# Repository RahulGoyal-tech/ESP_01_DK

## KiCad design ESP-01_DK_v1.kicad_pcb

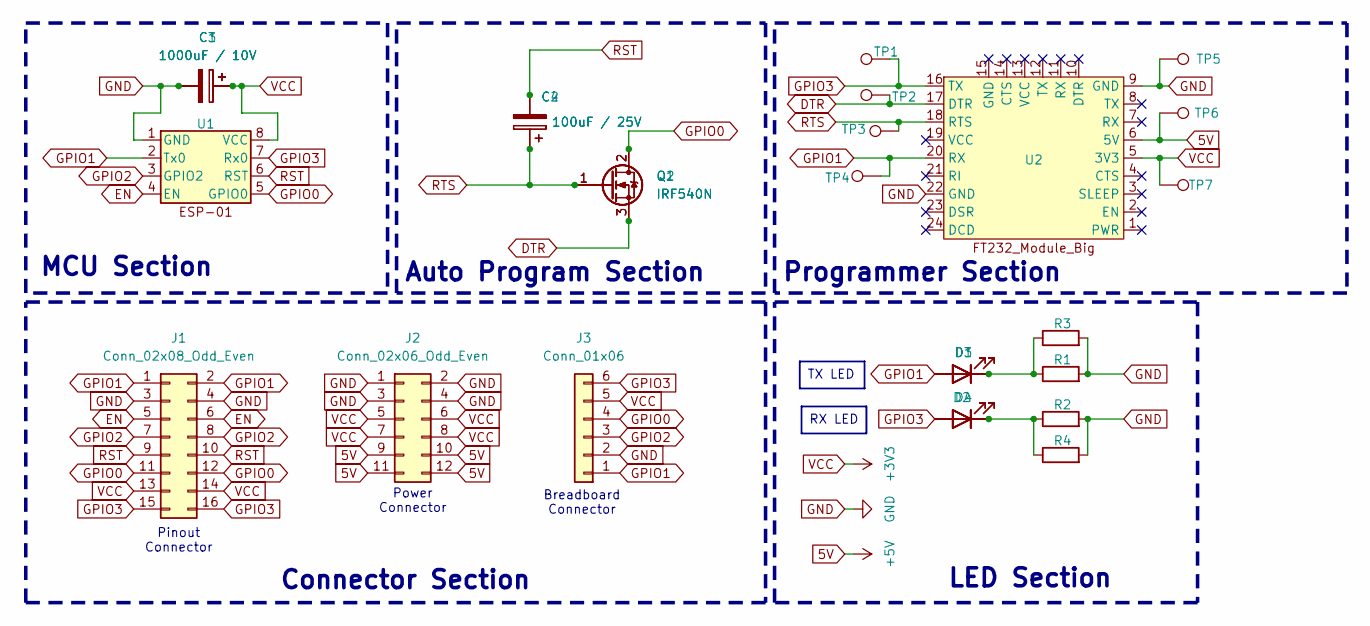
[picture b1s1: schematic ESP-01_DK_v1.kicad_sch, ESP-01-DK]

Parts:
C1: 1000uF / 10V; C_Radial_D10.0mm_H16.0mm_P5.00mm
C2: 100uF / 25V; C_Radial_D6.3mm_H11.0mm_P2.50mm
C3: 1000uF / 10V; C_Radial_D8.0mm_H11.5mm_P3.50mm
C4: 100uF / 25V; C_Radial_D4.0mm_H7.0mm_P1.50mm
D1, D2: LED; LED_D5.0mm
D3, D4: LED; LED_0805_2012Metric
J1: Conn_02x08_Odd_Even; PinHeader_2x08_P2.54mm_Vertical
J2: Conn_02x06_Odd_Even; PinHeader_2x06_P2.54mm_Vertical
J3: Conn_01x06; PinHeader_1x06_P2.54mm_Vertical
Q1: IRF540N; TO-220-3_Vertical
Q2: IRF540N; TO-252-2
R1, R2: 330; R_Axial_DIN0207_L6.3mm_D2.5mm_P10.16mm_Horizontal
R3, R4: 330; R_0805_2012Metric_Pad1.20x1.40mm_HandSolder
TP1, TP2: TestPoint_Bridge_Pitch2.54mm_Drill0.7mm
TP3, TP4, TP5, TP6, TP7: TestPoint; TestPoint_Bridge_Pitch2.54mm_Drill0.7mm
U1: PinHeader_2x04_P2.54mm_Vertical
U2: FT232_Module_Big

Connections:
5V: J2.9, J2.10, J2.11, J2.12, TP6.1, U2.6 (5V)
DTR: Q1.3 (S), Q2.3 (S), TP2.1, U2.17 (DTR)
EN: J1.5, J1.6, U1.4 (EN)
GND: C1.2, C3.2, J1.3, J1.4, J2.1, J2.2, J2.3, J2.4, J3.2, R1.2, R2.2, R3.2, R4.2, TP5.1, U1.1 (GND), U2.9 (GND), U2.22 (GND)
GPIO0: J1.11, J1.12, J3.4, Q1.2 (D), Q2.2 (D), U1.5 (GPIO0)
GPIO1: D1.2 (A), D3.2 (A), J1.1, J1.2, J3.1, TP4.1, U1.2 (Tx0), U2.20 (RX)
GPIO2: J1.7, J1.8, J3.3, U1.3 (GPIO2)
GPIO3: D2.2 (A), D4.2 (A), J1.15, J1.16, J3.6, TP1.1, U1.7 (Rx0), U2.16 (TX)
unnamed: D1.1 (K), D3.1 (K), R1.1, R3.1
unnamed: D2.1 (K), D4.1 (K), R2.1, R4.1
RST: C2.2, C4.2, J1.9, J1.10, U1.6 (RST)
RTS: C2.1, C4.1, Q1.1 (G), Q2.1 (G), TP3.1, U2.18 (RTS)
VCC: C1.1, C3.1, J1.13, J1.14, J2.5, J2.6, J2.7, J2.8, J3.5, TP7.1, U1.8 (VCC), U2.5 (3V3)

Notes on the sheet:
RX LED
TX LED
Auto Program Section
Programmer Section
Breadboard Connector
Connector Section
Power Connector
MCU Section
LED Section
Pinout Connector

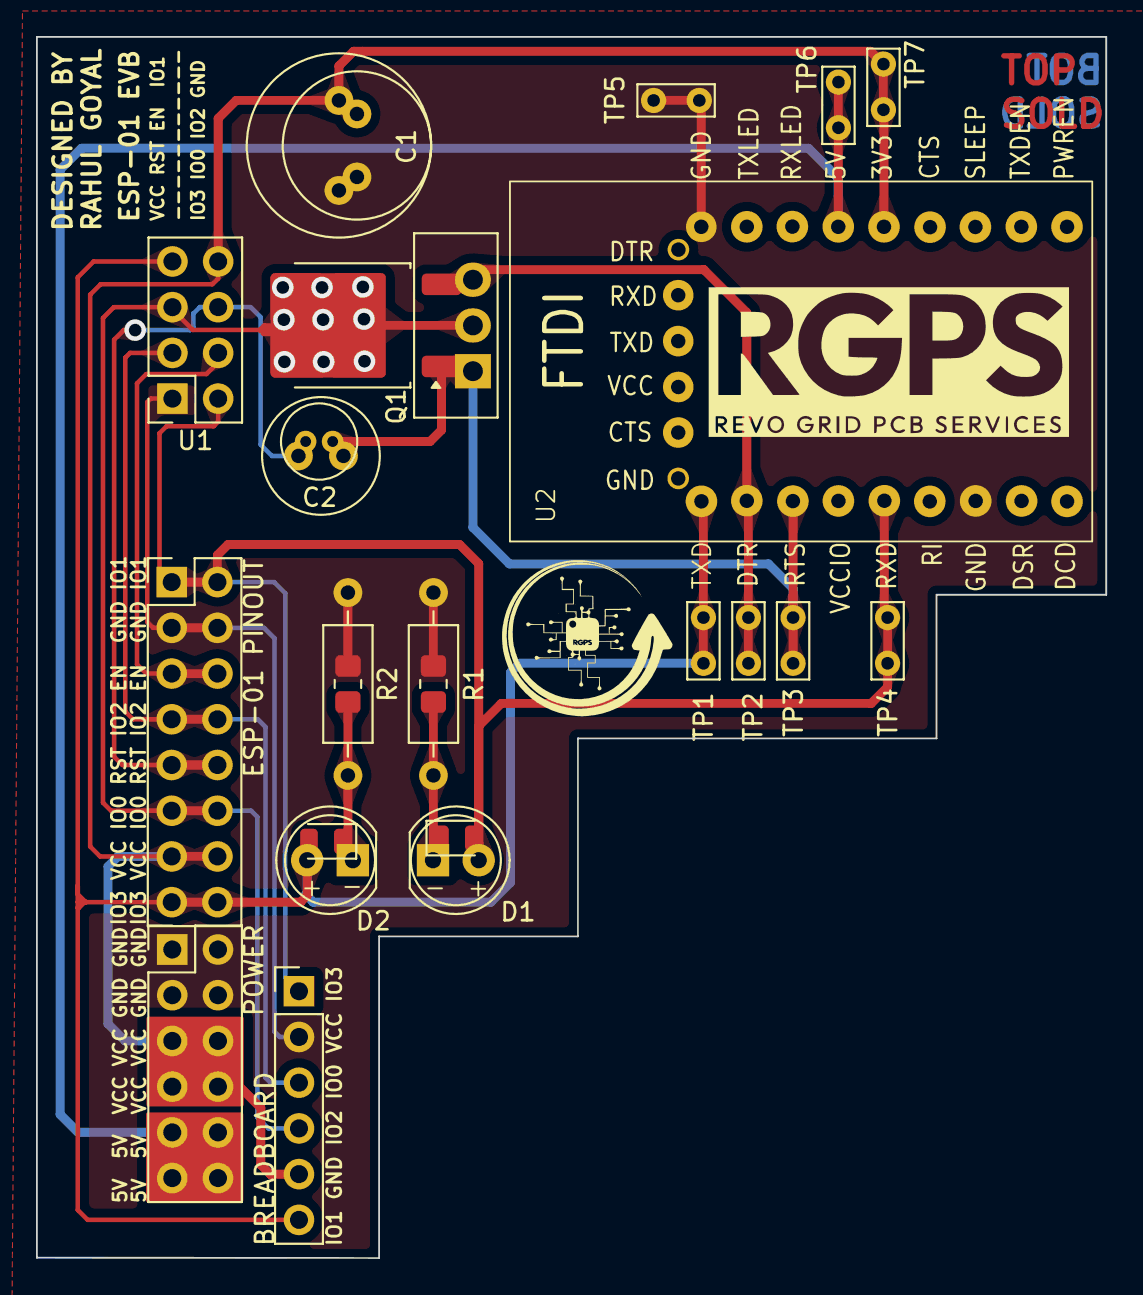
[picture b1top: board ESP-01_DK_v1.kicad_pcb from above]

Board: 2 copper layers, 59.4 x 67.8 mm, 26 parts (0 on the bottom side), 13 nets.
